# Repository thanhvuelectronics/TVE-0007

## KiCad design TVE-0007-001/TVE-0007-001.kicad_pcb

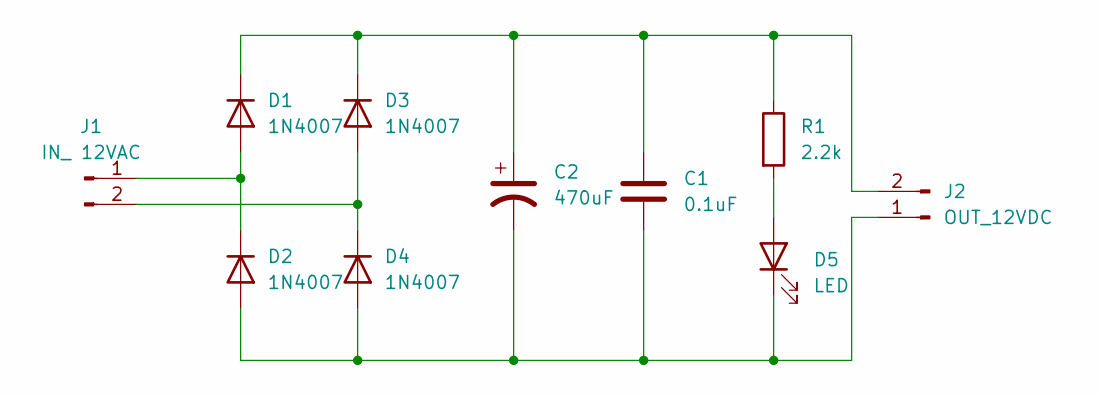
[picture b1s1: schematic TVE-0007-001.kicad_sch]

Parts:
C1: 0.1uF; C_Disc_D5.0mm_W2.5mm_P5.00mm
C2: 470uF; CP_Radial_D10.0mm_P5.00mm
D1, D2, D3, D4: 1N4007; D_DO-41_SOD81_P10.16mm_Horizontal
D5: LED; LED_D3.0mm
J1: IN_ 12VAC; PinHeader_1x02_P2.54mm_Vertical
J2: OUT_12VDC; PinHeader_1x02_P2.54mm_Vertical
R1: 2.2k; R_Axial_DIN0207_L6.3mm_D2.5mm_P7.62mm_Horizontal

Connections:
unnamed: D1.2 (A), D2.1 (K), J1.1
unnamed: C1.1, C2.1, D1.1 (K), D3.1 (K), J2.2, R1.1
unnamed: C1.2, C2.2, D2.2 (A), D4.2 (A), D5.1 (K), J2.1
unnamed: D3.2 (A), D4.1 (K), J1.2
unnamed: D5.2 (A), R1.2

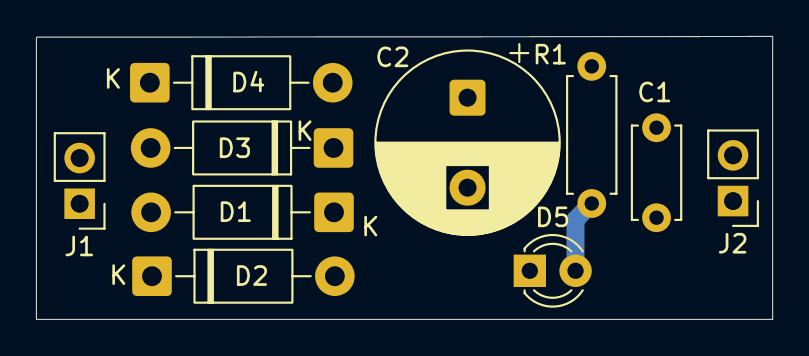
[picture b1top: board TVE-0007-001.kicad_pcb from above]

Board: 2 copper layers, 40.9 x 15.7 mm, 10 parts (0 on the bottom side), 5 nets.
